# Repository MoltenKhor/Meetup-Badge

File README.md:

# Meetup-Badge
An FR4 credit card sized badge that you can use to make your event or meetup more memorable.
This repo contains a version with solder pads and traces for a pro-micro controller and 2 MX switches but also a totally clean version if you don't want any component on it.

Photos, instructions will be added soon.

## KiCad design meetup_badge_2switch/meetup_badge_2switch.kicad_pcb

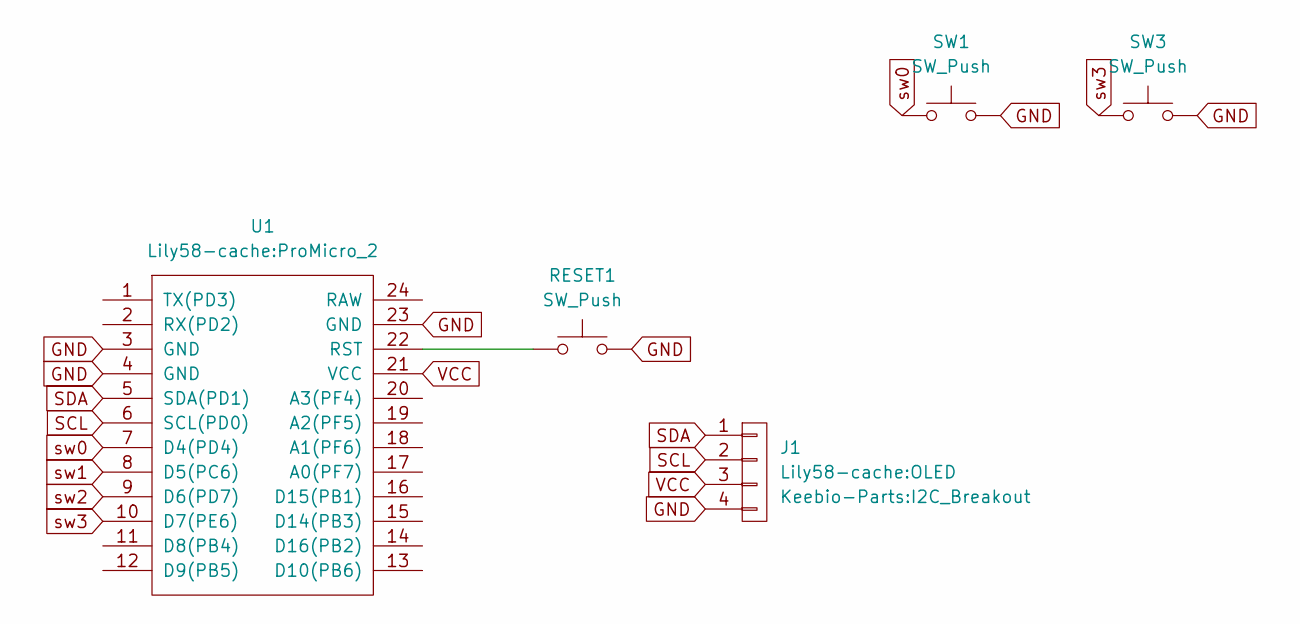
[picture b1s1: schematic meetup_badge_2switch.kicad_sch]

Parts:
J1: Lily58-cache:OLED; I2C_Breakout
RESET1: SW_Push; D_A-405_P2.54mm_Vertical_KathodeUp
SW1, SW3: SW_Push; MXOnly-1U-NoLED
U1: Lily58-cache:ProMicro_2; ArduinoProMicro-BackSide

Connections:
GND: J1.4, RESET1.2, SW1.2, SW3.2, U1.3 (GND), U1.4 (GND), U1.23 (GND)
unnamed: RESET1.1, U1.22 (RST)
SCL: J1.2, U1.6 (SCL(PD0))
SDA: J1.1, U1.5 (SDA(PD1))
VCC: J1.3, U1.21 (VCC)
sw0: SW1.1, U1.7 (D4(PD4))
sw1: U1.8 (D5(PC6))
sw2: U1.9 (D6(PD7))
sw3: SW3.1, U1.10 (D7(PE6))

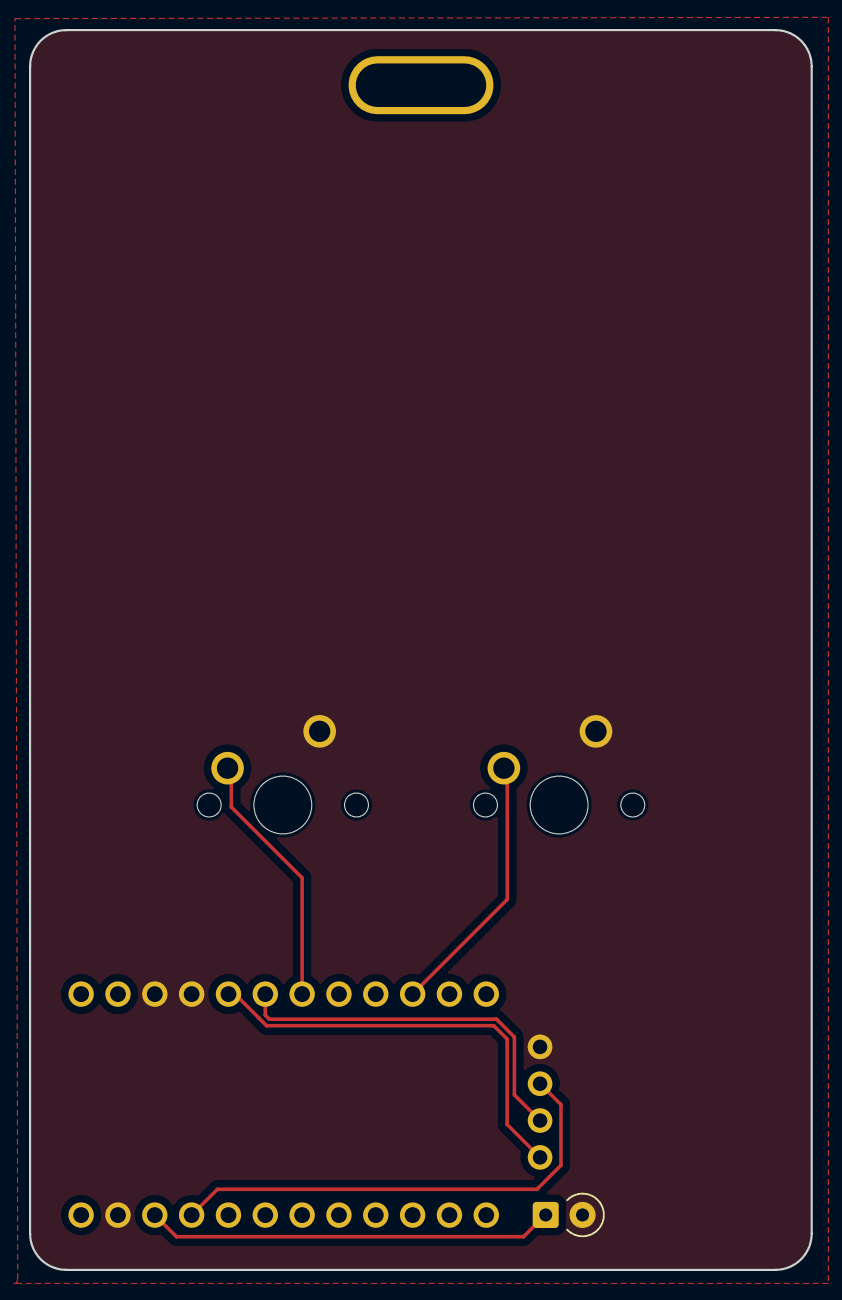
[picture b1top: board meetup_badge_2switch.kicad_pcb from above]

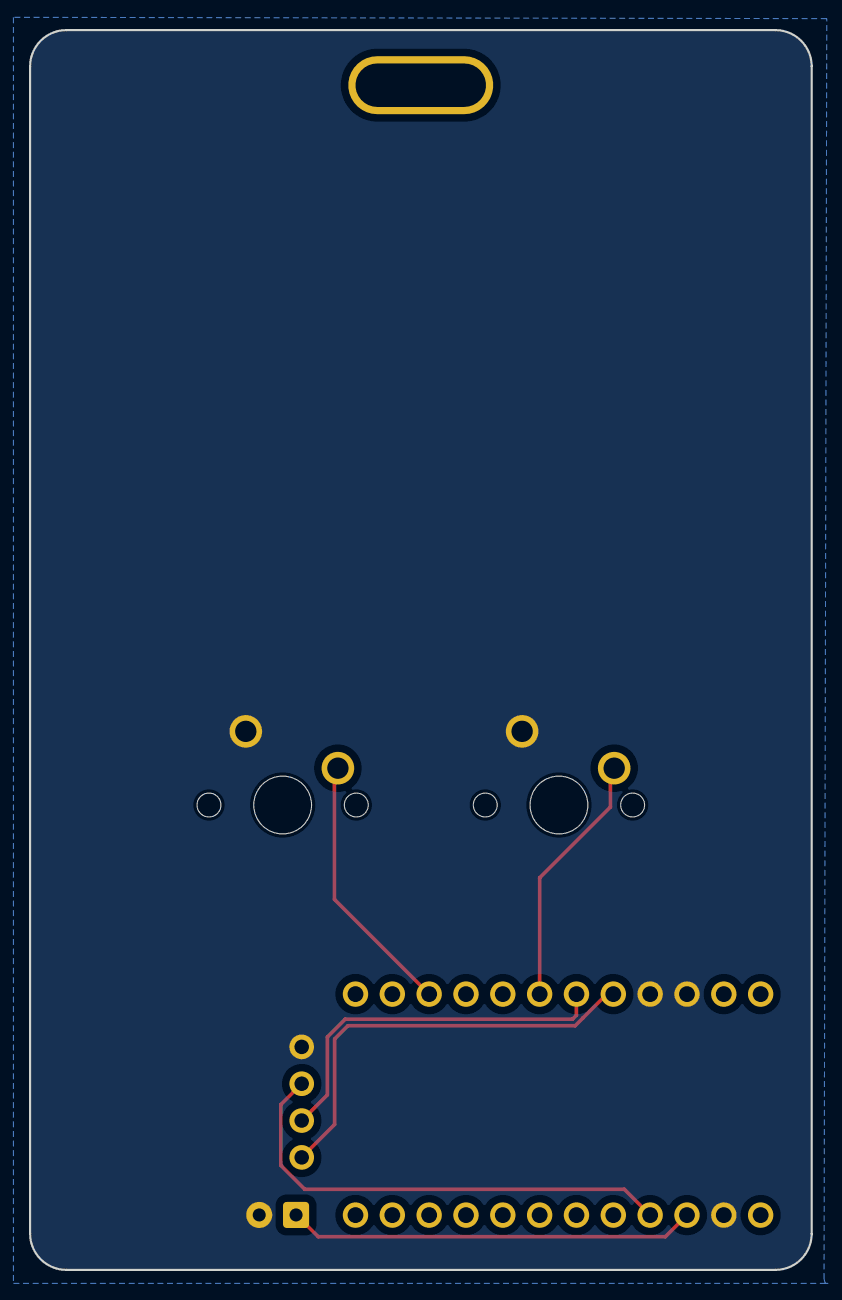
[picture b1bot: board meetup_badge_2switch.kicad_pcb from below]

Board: 2 copper layers, 53.9 x 85.5 mm, 5 parts (2 on the bottom side), 7 nets.

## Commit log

2026-01-25 first upload
2026-04-17 Create firmware
2026-04-17 added fw
